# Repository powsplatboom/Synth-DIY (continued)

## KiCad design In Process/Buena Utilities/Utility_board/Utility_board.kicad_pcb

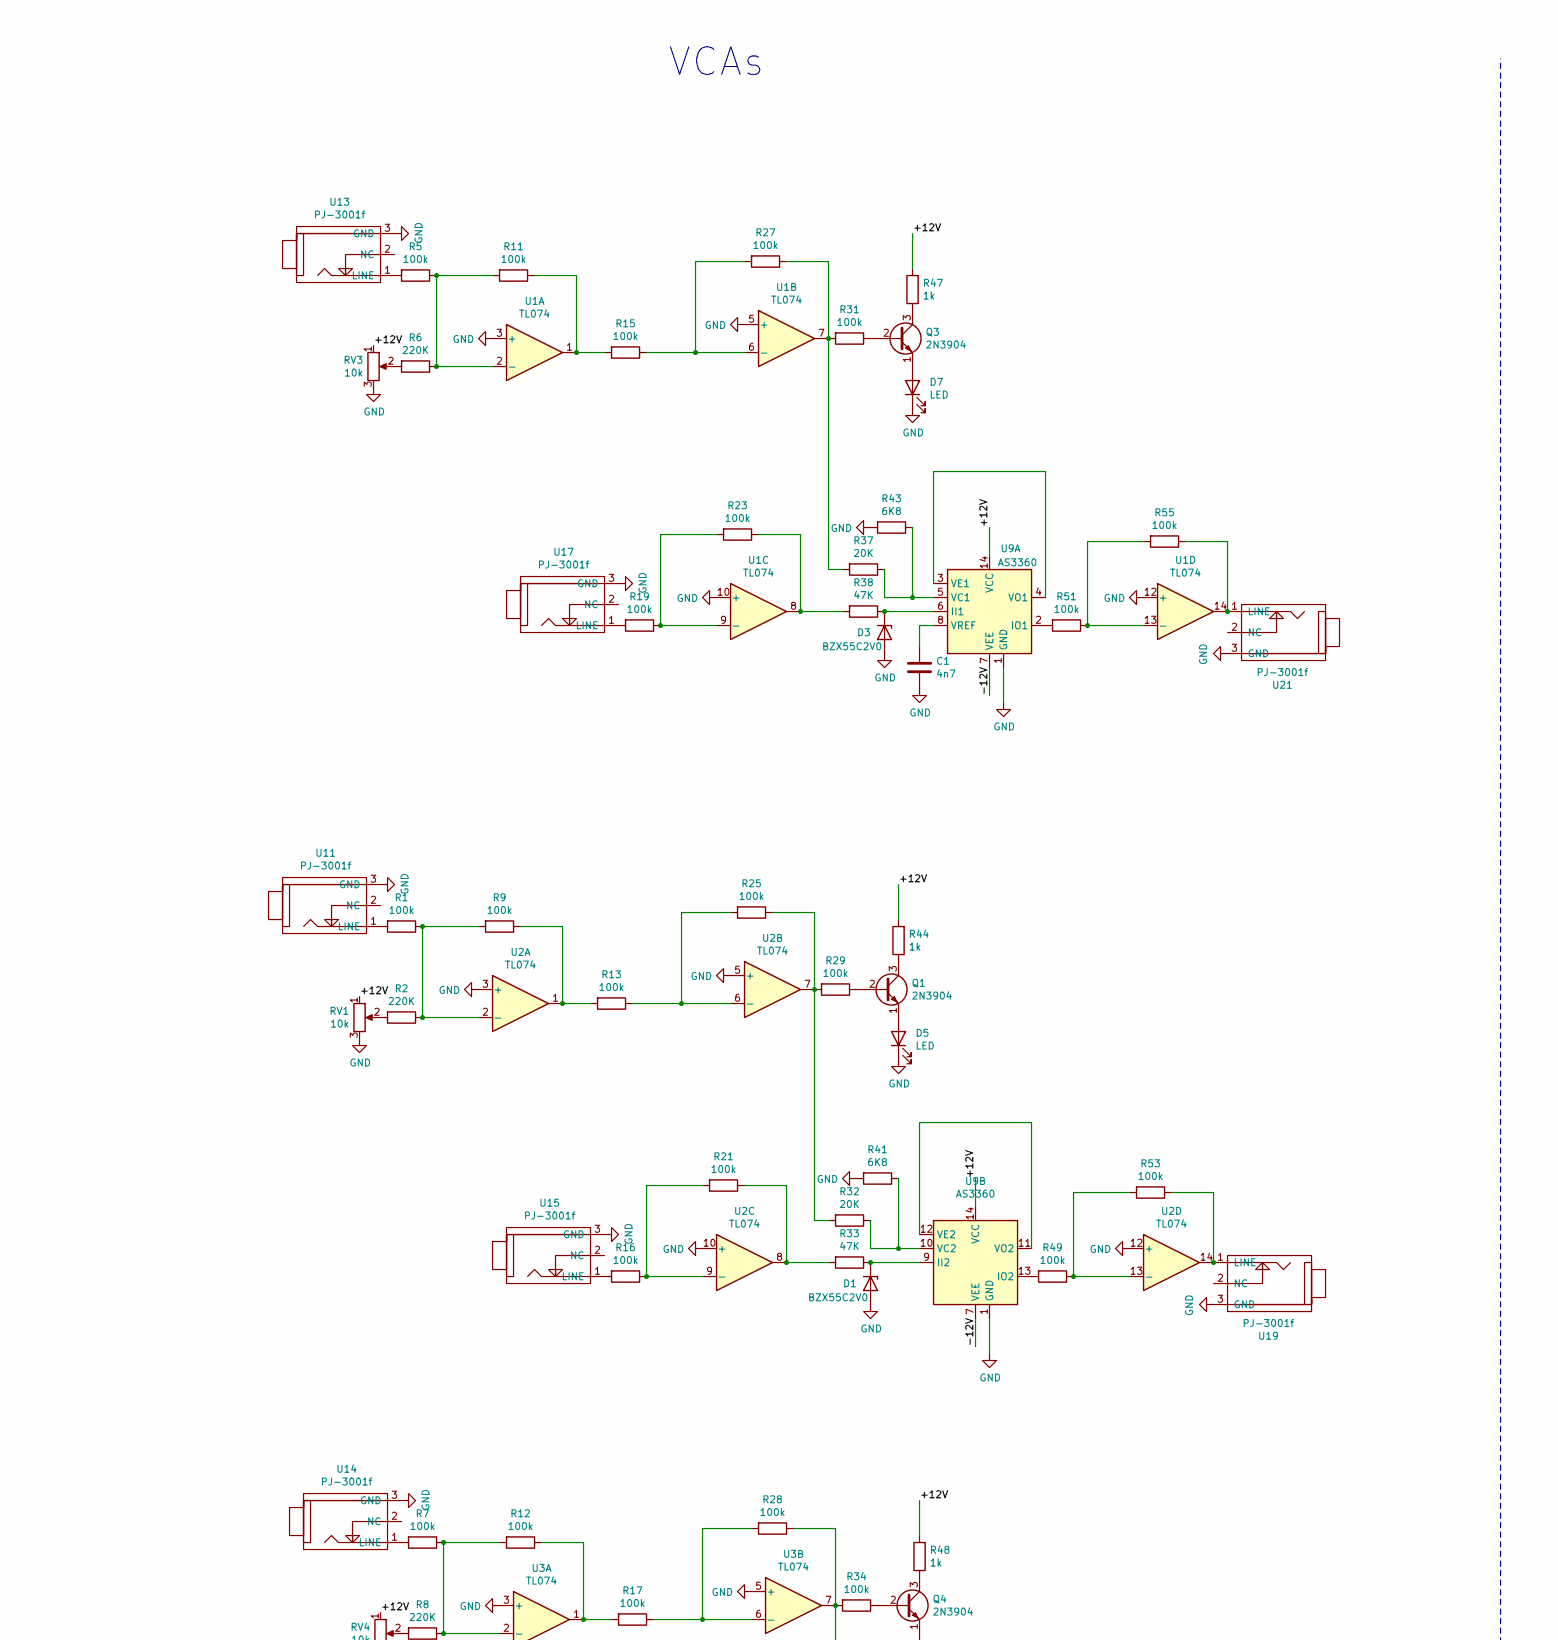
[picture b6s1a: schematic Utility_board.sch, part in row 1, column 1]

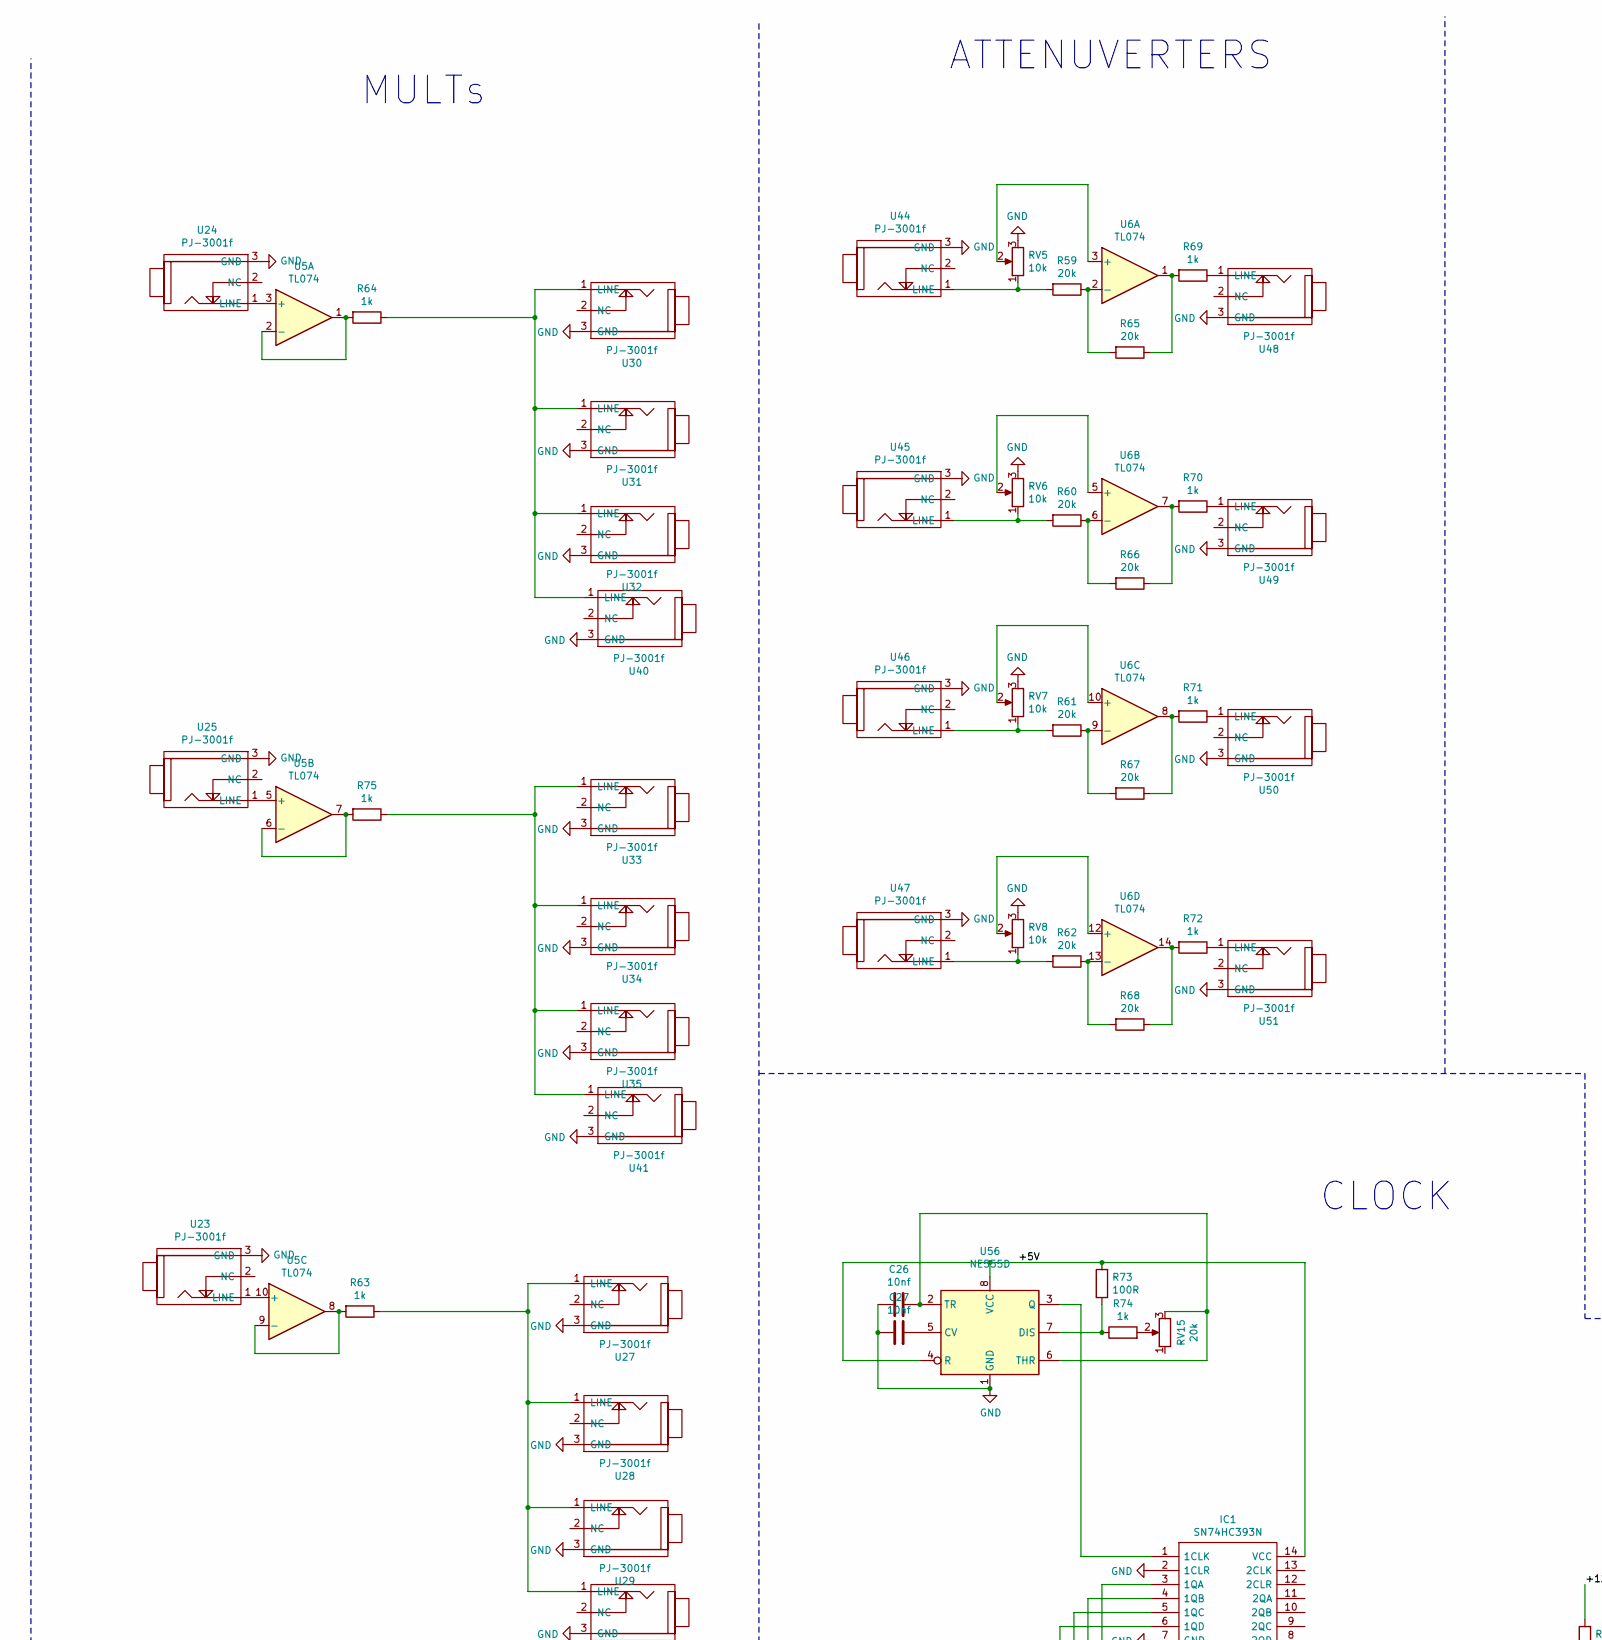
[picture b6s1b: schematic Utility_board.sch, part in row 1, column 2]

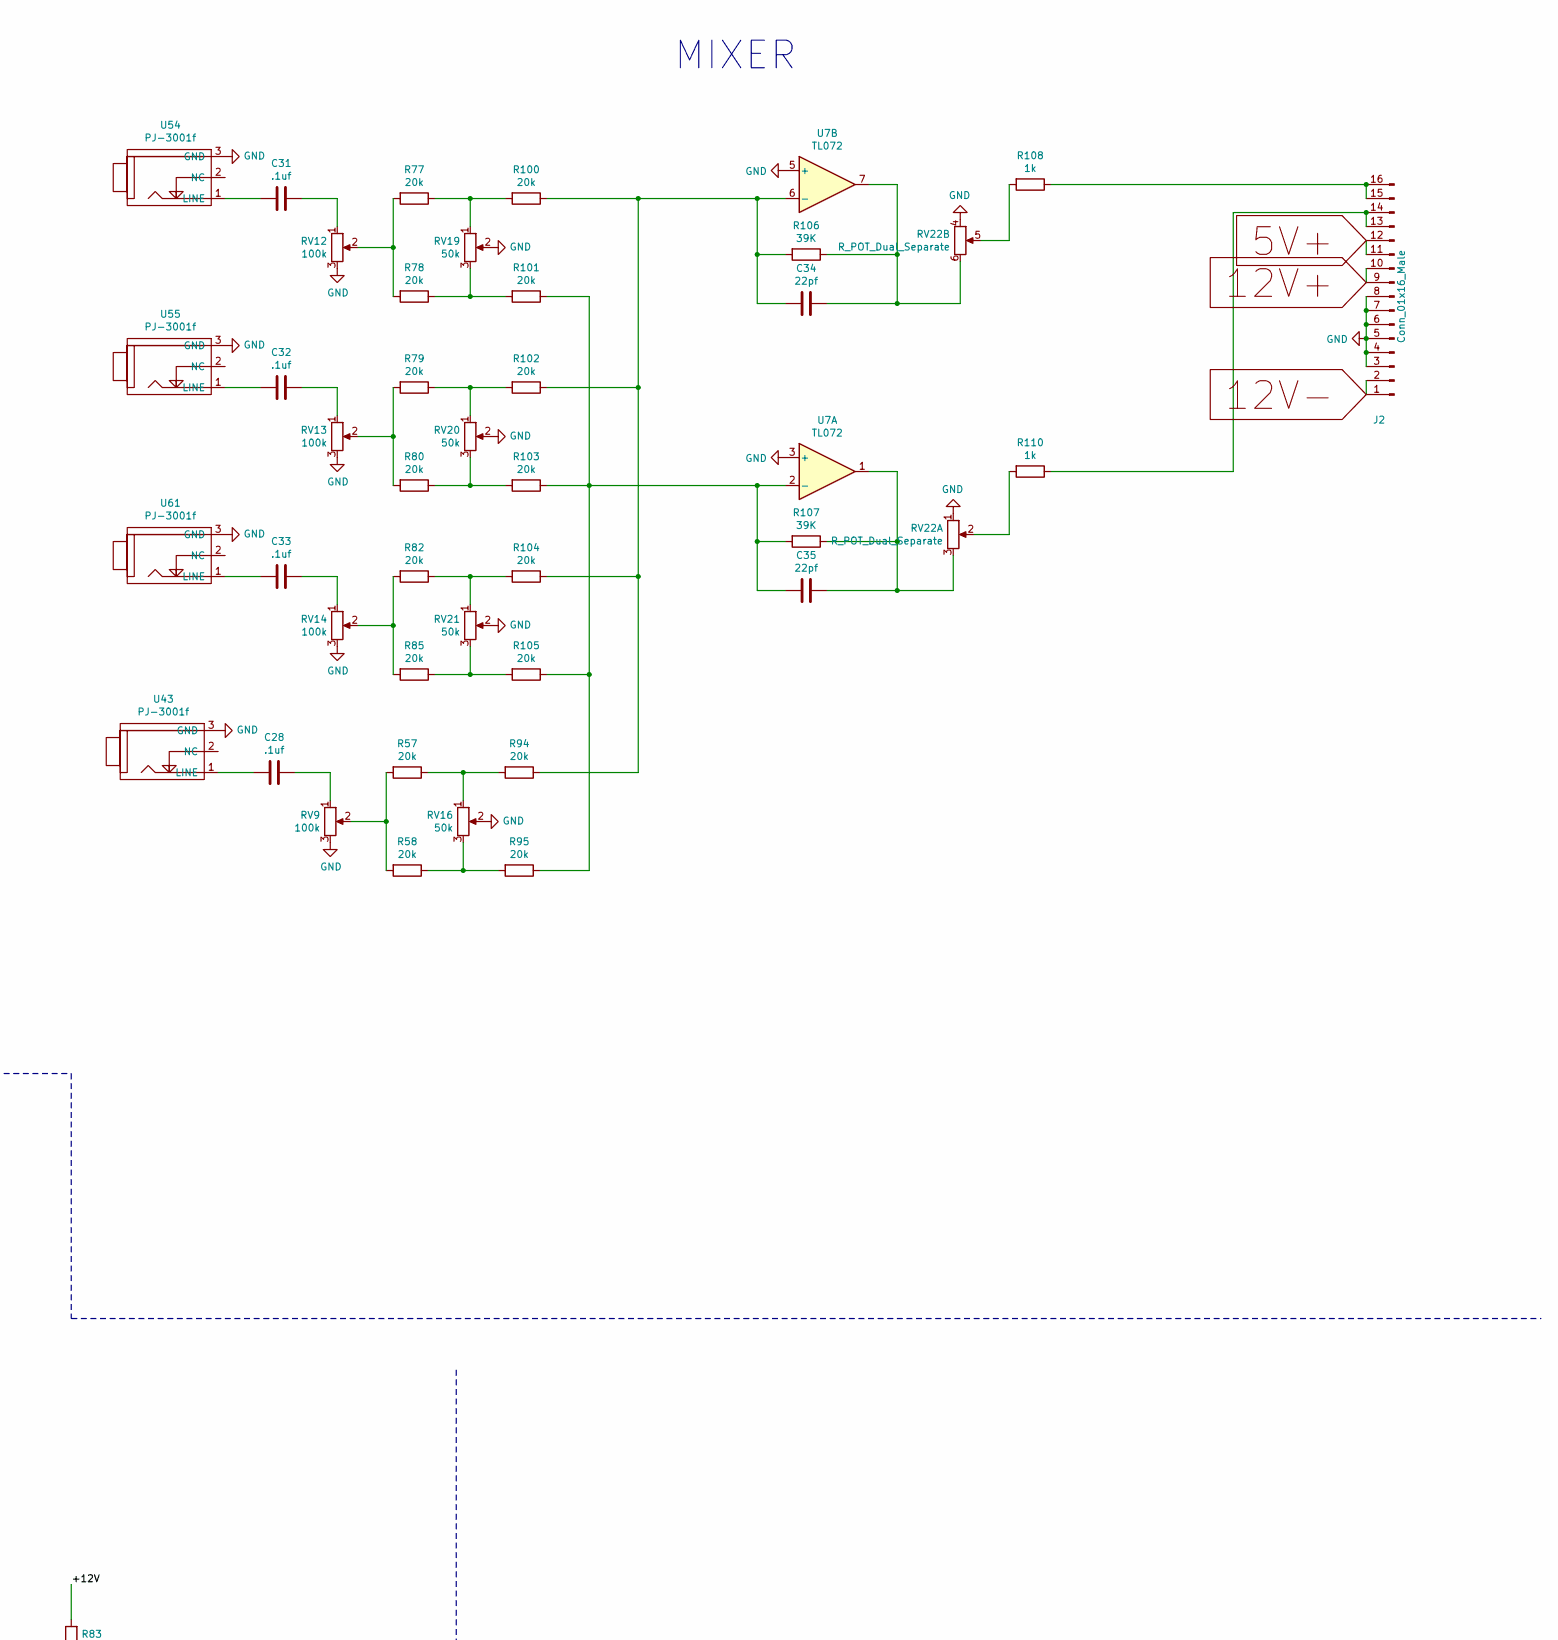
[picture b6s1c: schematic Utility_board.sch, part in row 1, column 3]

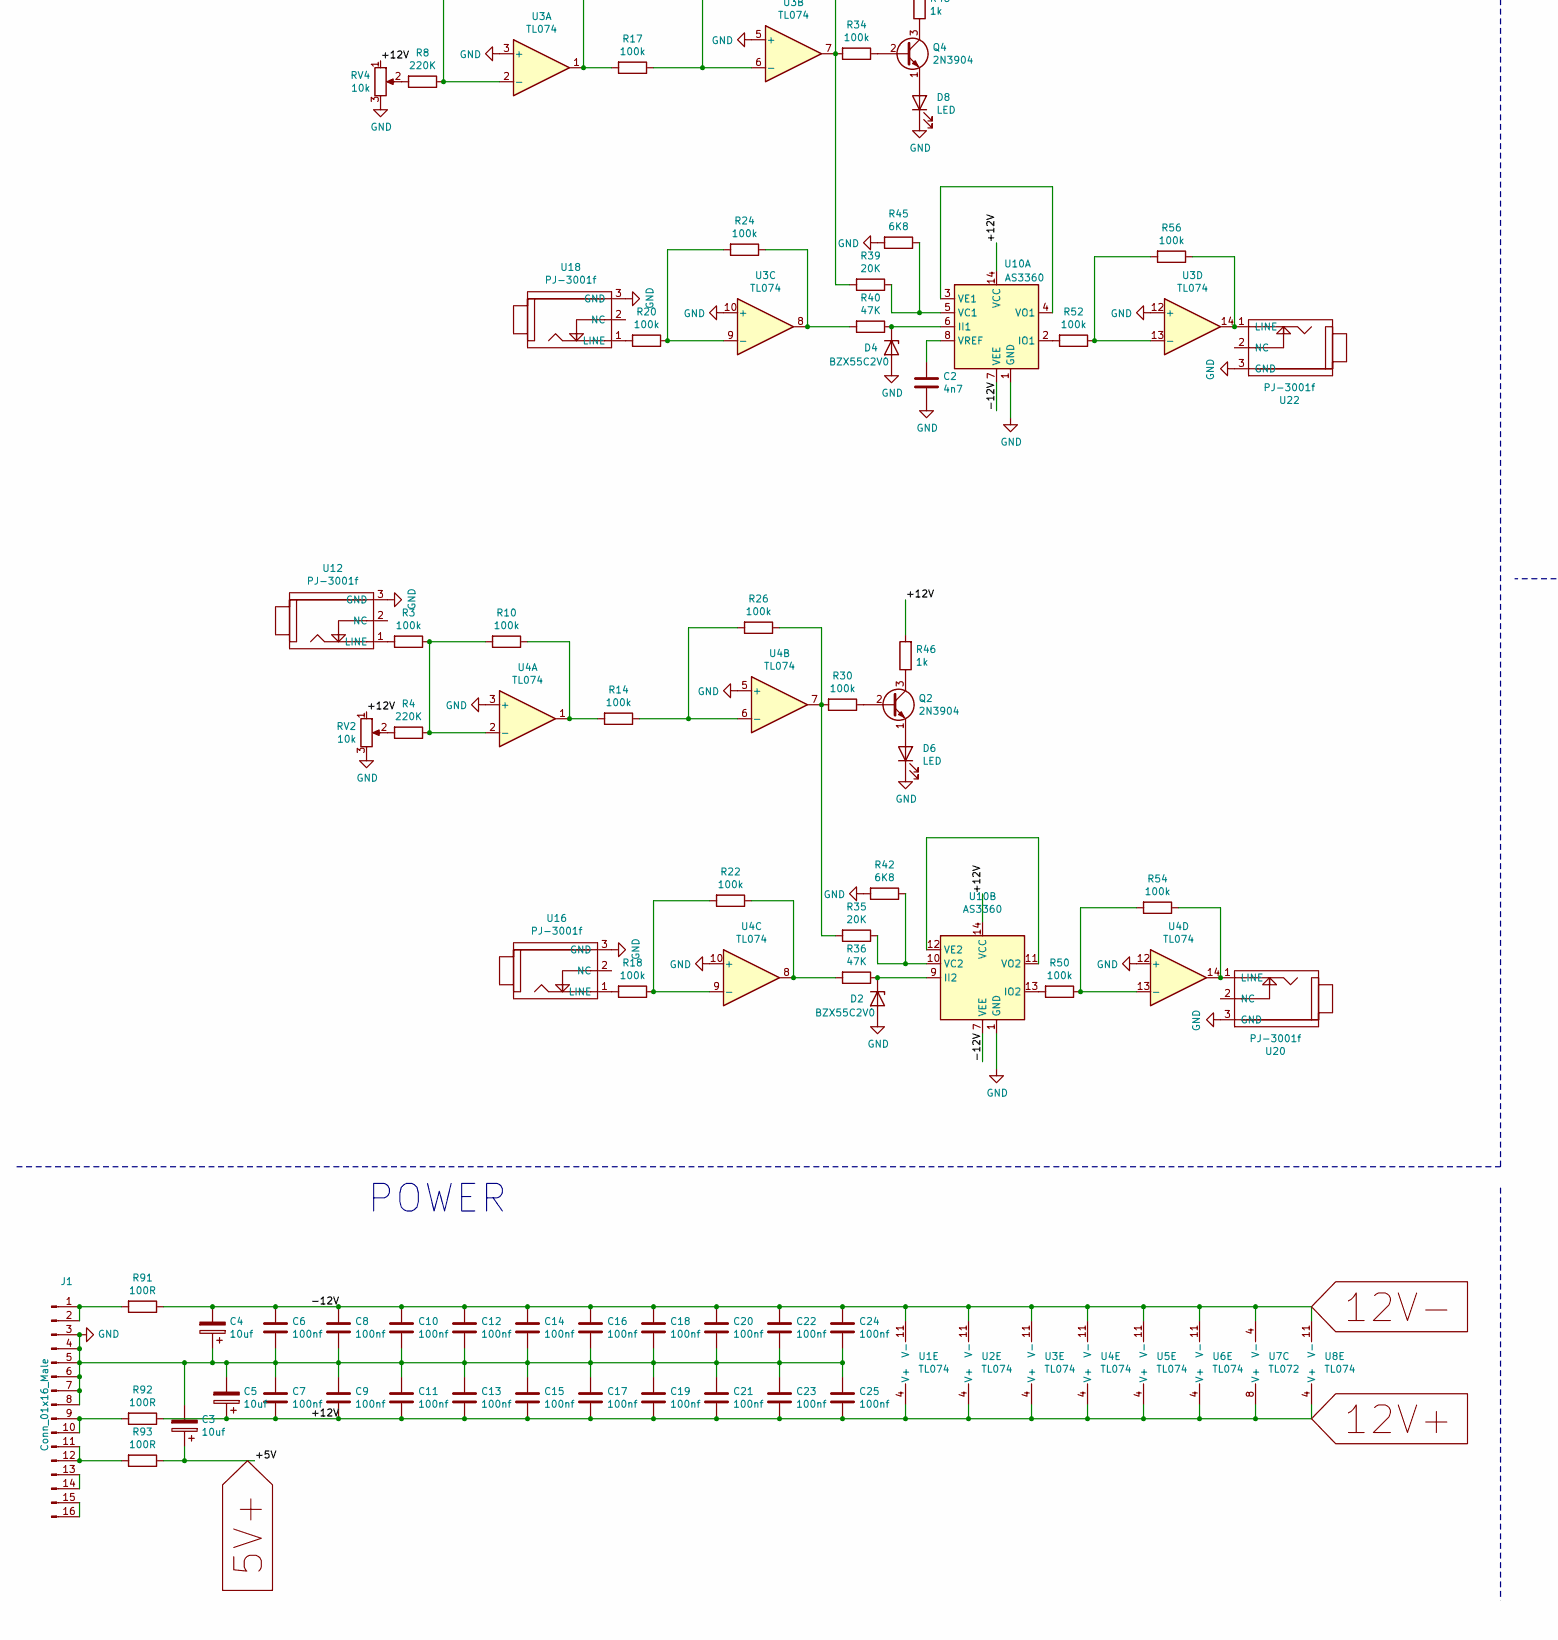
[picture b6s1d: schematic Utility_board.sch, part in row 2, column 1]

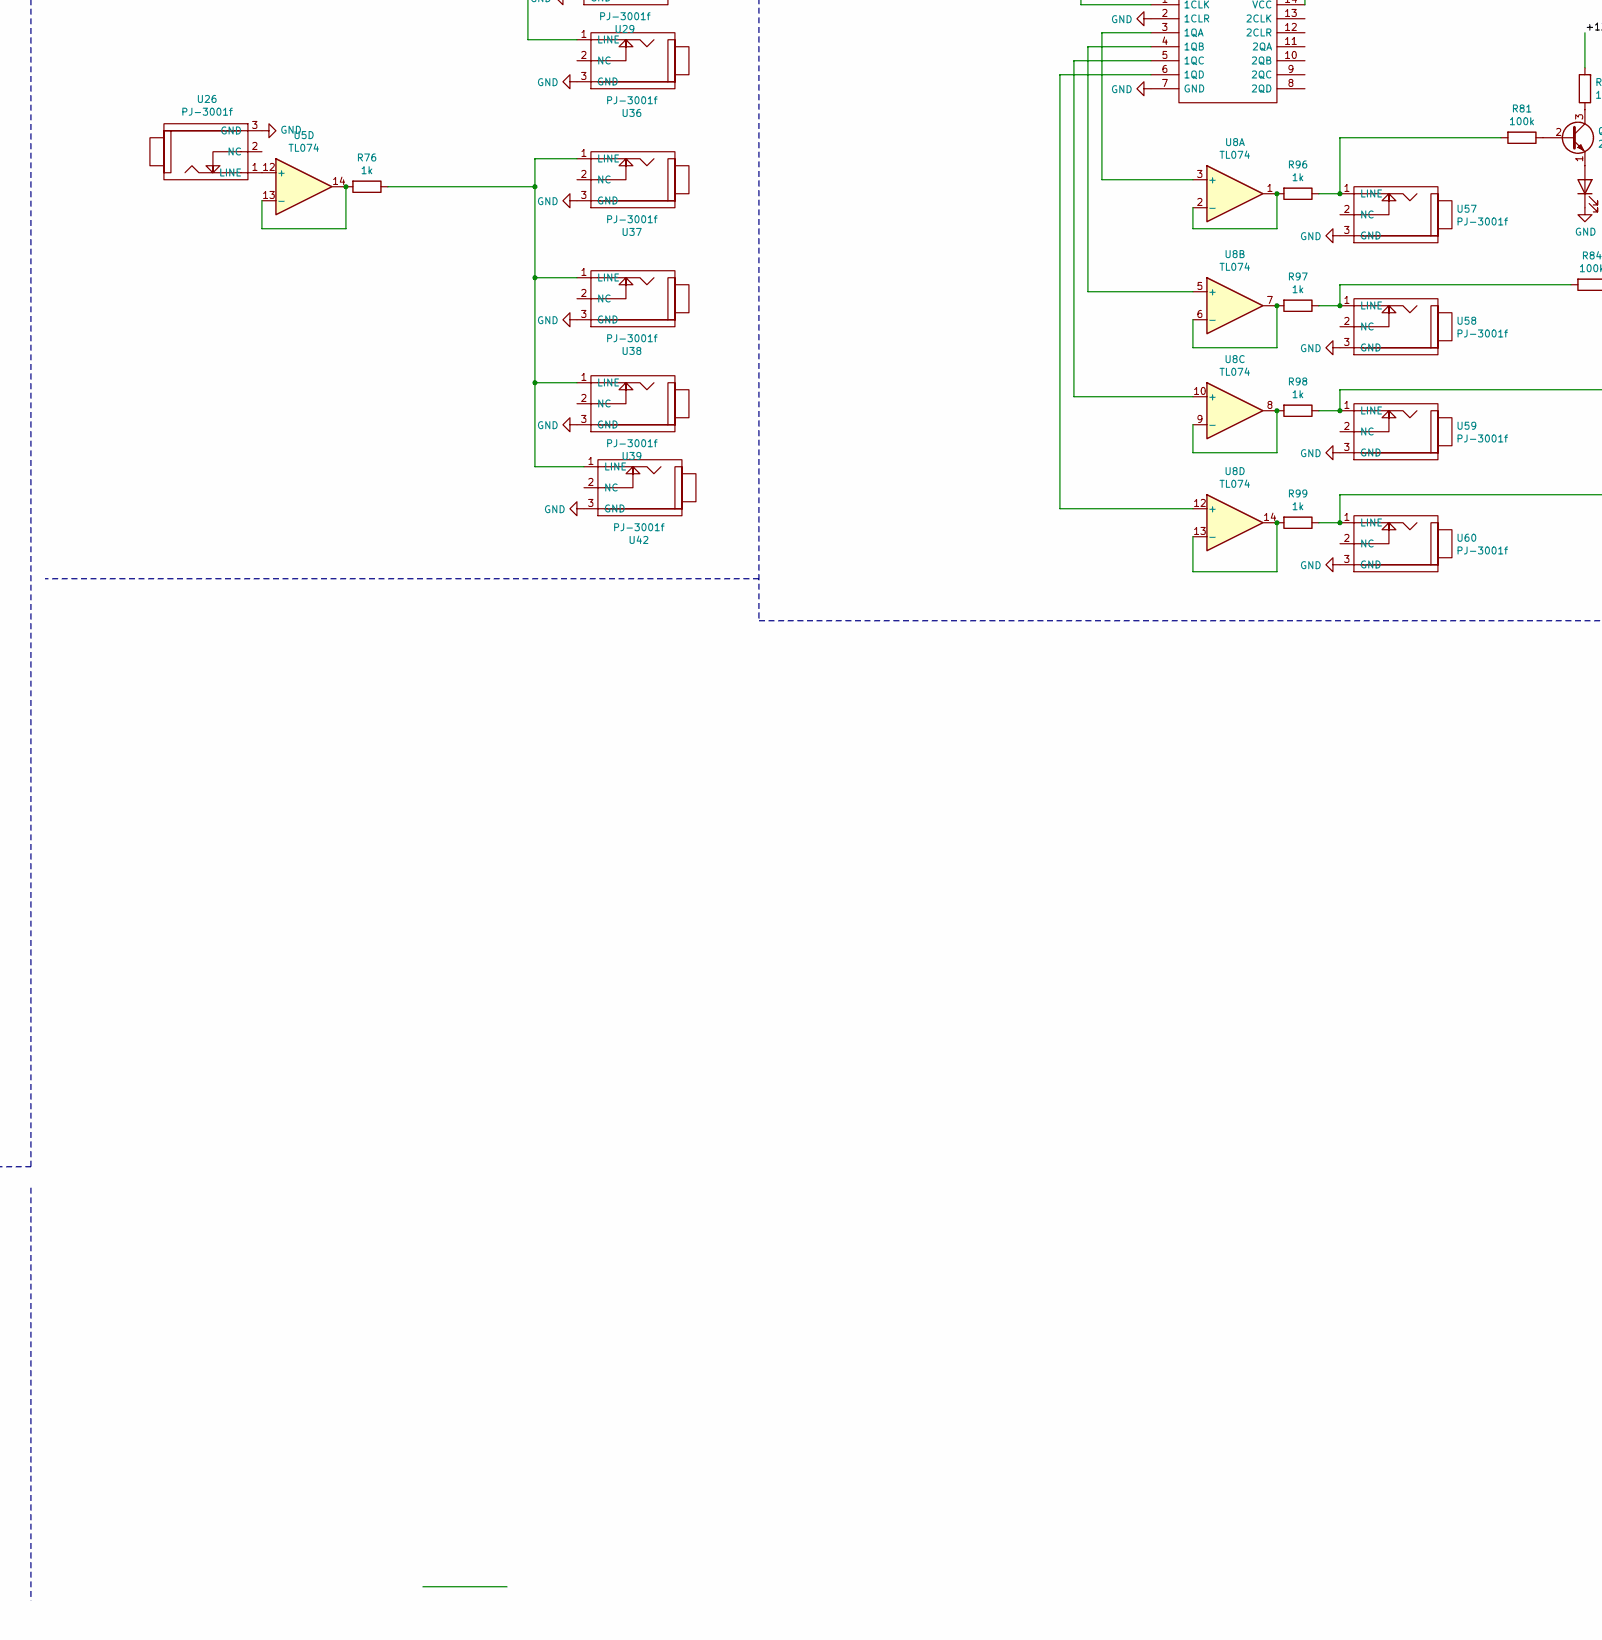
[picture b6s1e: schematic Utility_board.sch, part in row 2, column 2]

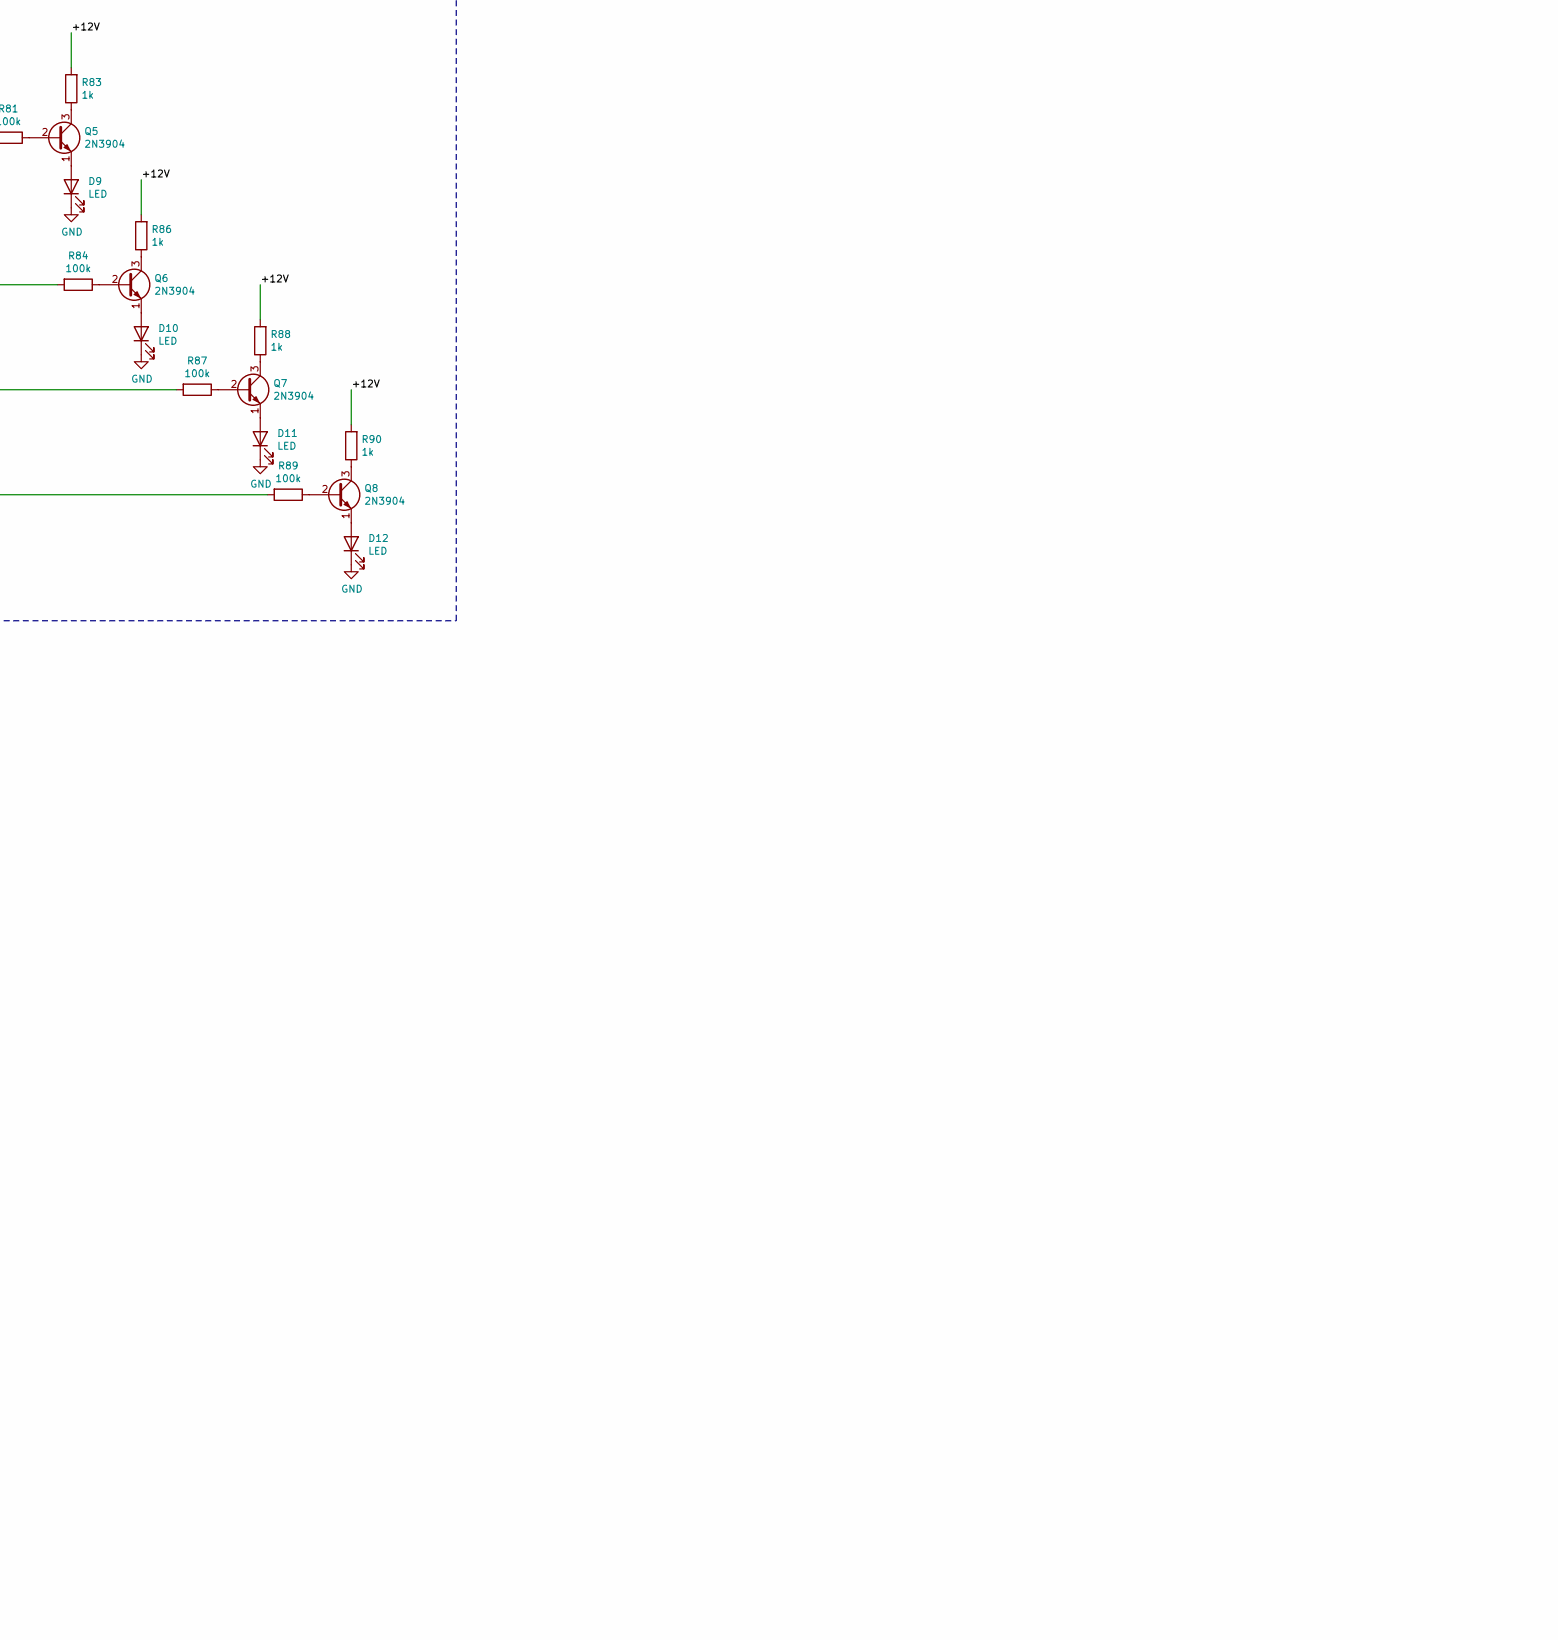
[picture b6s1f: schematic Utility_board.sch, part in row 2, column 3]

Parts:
C1, C2: 4n7; C_Disc_D4.3mm_W1.9mm_P5.00mm
C3, C4, C5: 10uf; CP_Radial_D5.0mm_P2.50mm
C6, C7, C8, C9, C10, C11, C12, C13, C14, C15, C16, C17, C18, C19, C20, C21, C22, C23, C24, C25: 100nf; C_Disc_D4.3mm_W1.9mm_P5.00mm
C26, C27: 10nf; C_Disc_D4.3mm_W1.9mm_P5.00mm
C28, C31, C32, C33: .1uf; C_Disc_D4.3mm_W1.9mm_P5.00mm
C34, C35: 22pf; C_Disc_D4.3mm_W1.9mm_P5.00mm
D1, D2, D3, D4: BZX55C2V0; D_DO-34_SOD68_P7.62mm_Horizontal
D5, D6, D7, D8, D9, D10, D11, D12: LED; LED_D5.0mm
IC1: SN74HC393N; DIP-14_W7.62mm_Socket; Manufacturer_Part_Number SN74HC393N; Mouser Part Number 595-SN74HC393N
J1, J2: Conn_01x16_Male; IDC-Header_2x08_P2.54mm_Vertical
Q1, Q2, Q3, Q4, Q5, Q6, Q7, Q8: 2N3904; TO-92_Inline
R1, R3, R5, R7, R9, R10, R11, R12, R13, R14, R15, R16, R17, R18, R19, R20, R21, R22, R23, R24, R25, R26, R27, R28, R29, R30, R31, R34, R49, R50, R51, R52, R53, R54, R55, R56, R81, R84, R87, R89: 100k; R_Axial_DIN0204_L3.6mm_D1.6mm_P7.62mm_Horizontal
R2, R4, R6, R8: 220K; R_Axial_DIN0204_L3.6mm_D1.6mm_P7.62mm_Horizontal
R32, R35, R37, R39: 20K; R_Axial_DIN0204_L3.6mm_D1.6mm_P7.62mm_Horizontal
R33, R36, R38, R40: 47K; R_Axial_DIN0204_L3.6mm_D1.6mm_P7.62mm_Horizontal
R41, R42, R43, R45: 6K8; R_Axial_DIN0204_L3.6mm_D1.6mm_P7.62mm_Horizontal
R44, R46, R47, R48, R63, R64, R69, R70, R71, R72, R74, R75, R76, R83, R86, R88, R90, R96, R97, R98, R99, R108, R110: 1k; R_Axial_DIN0204_L3.6mm_D1.6mm_P7.62mm_Horizontal
R57, R58, R59, R60, R61, R62, R65, R66, R67, R68, R77, R78, R79, R80, R82, R85, R94, R95, R100, R101, R102, R103, R104, R105: 20k; R_Axial_DIN0204_L3.6mm_D1.6mm_P7.62mm_Horizontal
R73, R91, R92, R93: 100R; R_Axial_DIN0204_L3.6mm_D1.6mm_P7.62mm_Horizontal
R106, R107: 39K; R_Axial_DIN0204_L3.6mm_D1.6mm_P7.62mm_Horizontal
RV1, RV2, RV3, RV4, RV5, RV6, RV7, RV8: 10k; Potentiometer_Alpha_RD901F-40-00D_Single_Vertical_CircularH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
RV9, RV12, RV13, RV14: 100k; Potentiometer_Alpha_RD901F-40-00D_Single_Vertical_CircularH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
RV15: 20k; Potentiometer_Alpha_RD901F-40-00D_Single_Vertical_CircularH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
RV16, RV19, RV20, RV21: 50k; Potentiometer_Alpha_RD901F-40-00D_Single_Vertical_CircularH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
RV22: R_POT_Dual_Separate; Potentiometer_Alpha_RD902F-40-00D_Dual_Vertical_CircularHol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
U1, U2, U3, U4, U5, U6, U8: TL074; DIP-14_W7.62mm_Socket
U7: TL072; DIP-8_W7.62mm_Socket
U9, U10: AS3360; DIP-14_W7.62mm_Socket
U11, U12, U13, U14, U15, U16, U17, U18, U19, U20, U21, U22, U23, U24, U25, U26, U27, U28, U29, U30, U31, U32, U33, U34, U35, U36, U37, U38, U39, U40, U41, U42, U43, U44, U45, U46, U47, U48, U49, U50, U51, U54, U55, U57, U58, U59, U60, U61: PJ-3001f; PJ-3001_Mono_Phone
U56: NE555D; DIP-8_W7.62mm_Socket

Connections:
5V+: C3.1, IC1.14 (VCC), J2.11, J2.12, R73.2, R93.1, U56.4 (R), U56.8 (VCC)
12V+: C5.1, C7.2, C9.2, C11.2, C13.2, C15.2, C17.2, C19.2, C21.2, C23.2, C25.2, J2.9, J2.10, R44.2, R46.2, R47.2, R48.2, R83.2, R86.2, R88.2, R90.2, R92.1, RV1.1, RV2.1, RV3.1, RV4.1, U1.4 (V+), U2.4 (V+), U3.4 (V+), U4.4 (V+), U5.4 (V+), U6.4 (V+), U7.8 (V+), U8.4 (V+), U9.14 (VCC), U10.14 (VCC)
12V-: C4.2, C6.1, C8.1, C10.1, C12.1, C14.1, C16.1, C18.1, C20.1, C22.1, C24.1, J2.1, J2.2, R91.1, U1.11 (V-), U2.11 (V-), U3.11 (V-), U4.11 (V-), U5.11 (V-), U6.11 (V-), U7.4 (V-), U8.11 (V-), U9.7 (VEE), U10.7 (VEE)
GND: C1.2, C2.2, C3.2, C4.1, C5.2, C6.2, C7.1, C8.2, C9.1, C10.2, C11.1, C12.2, C13.1, C14.2, C15.1, C16.2, C17.1, C18.2, C19.1, C20.2, C21.1, C22.2, C23.1, C24.2, C25.1, C26.2, C27.2, D1.2 (A), D2.2 (A), D3.2 (A), D4.2 (A), D5.1 (K), D6.1 (K), D7.1 (K), D8.1 (K), D9.1 (K), D10.1 (K), D11.1 (K), D12.1 (K), IC1.2 (1CLR), IC1.7 (GND), J1.3, J1.4, J1.5, J1.6, J1.7, J1.8, J2.3, J2.4, J2.5, J2.6, J2.7, J2.8, R41.2, R42.2, R43.2, R45.2, RV1.3, RV2.3, RV3.3, RV4.3, RV5.3, RV6.3, RV7.3, RV8.3, RV9.3, RV12.3, RV13.3, RV14.3, RV16.2, RV19.2, RV20.2, RV21.2, RV22.1, RV22.4, U1.3 (+), U1.5 (+), U1.10 (+), U1.12 (+), U2.3 (+), U2.5 (+), U2.10 (+), U2.12 (+), U3.3 (+), U3.5 (+), U3.10 (+), U3.12 (+), U4.3 (+), U4.5 (+), U4.10 (+), U4.12 (+), U7.3 (+), U7.5 (+), U9.1 (GND), U10.1 (GND), U11.3 (GND), U12.3 (GND), U13.3 (GND), U14.3 (GND), U15.3 (GND), U16.3 (GND), U17.3 (GND), U18.3 (GND), U19.3 (GND), U20.3 (GND), U21.3 (GND), U22.3 (GND), U23.3 (GND), U24.3 (GND), U25.3 (GND), U26.3 (GND), U27.3 (GND), U28.3 (GND), U29.3 (GND), U30.3 (GND), U31.3 (GND), U32.3 (GND), U33.3 (GND), U34.3 (GND), U35.3 (GND), U36.3 (GND), U37.3 (GND), U38.3 (GND), U39.3 (GND), U40.3 (GND), U41.3 (GND), U42.3 (GND), U43.3 (GND), U44.3 (GND), U45.3 (GND), U46.3 (GND), U47.3 (GND), U48.3 (GND), U49.3 (GND), U50.3 (GND), U51.3 (GND), U54.3 (GND), U55.3 (GND), U56.1 (GND), U57.3 (GND), U58.3 (GND), U59.3 (GND), U60.3 (GND), U61.3 (GND)
unnamed: C1.1, U9.8 (VREF)
unnamed: C2.1, U10.8 (VREF)
unnamed: C26.1, RV15.3, U56.2 (TR), U56.6 (THR)
unnamed: C27.1, U56.5 (CV)
unnamed: C28.1, RV9.1
unnamed: C28.2, U43.1 (LINE)
unnamed: C31.1, RV12.1
unnamed: C31.2, U54.1 (LINE)
unnamed: C32.1, RV13.1
unnamed: C32.2, U55.1 (LINE)
unnamed: C33.1, RV14.1
unnamed: C33.2, U61.1 (LINE)
unnamed: C34.1, R106.1, RV22.6, U7.7
unnamed: C34.2, R94.1, R100.1, R102.1, R104.1, R106.2, U7.6 (-)
unnamed: C35.1, R107.1, RV22.3, U7.1
unnamed: C35.2, R95.1, R101.1, R103.1, R105.1, R107.2, U7.2 (-)
unnamed: D1.1 (K), R33.1, U9.9 (II2)
unnamed: D2.1 (K), R36.1, U10.9 (II2)
unnamed: D3.1 (K), R38.1, U9.6 (II1)
unnamed: D4.1 (K), R40.1, U10.6 (II1)
unnamed: D5.2 (A), Q1.1 (E)
unnamed: D6.2 (A), Q2.1 (E)
unnamed: D7.2 (A), Q3.1 (E)
unnamed: D8.2 (A), Q4.1 (E)
unnamed: D9.2 (A), Q5.1 (E)
unnamed: D10.2 (A), Q6.1 (E)
unnamed: D11.2 (A), Q7.1 (E)
unnamed: D12.2 (A), Q8.1 (E)
unnamed: IC1.1 (1CLK), U56.3 (Q)
unnamed: IC1.3 (1QA), U8.3 (+)
unnamed: IC1.4 (1QB), U8.5 (+)
unnamed: IC1.5 (1QC), U8.10 (+)
unnamed: IC1.6 (1QD), U8.12 (+)
unnamed: J1.1, J1.2, R91.2
unnamed: J1.9, J1.10, R92.2
unnamed: J1.11, J1.12, R93.2
unnamed: J1.13, J1.14
unnamed: J1.15, J1.16
unnamed: J2.13, J2.14, R110.1
unnamed: J2.15, J2.16, R108.1
unnamed: Q1.2 (B), R29.1
unnamed: Q1.3 (C), R44.1
unnamed: Q2.2 (B), R30.1
unnamed: Q2.3 (C), R46.1
unnamed: Q3.2 (B), R31.1
unnamed: Q3.3 (C), R47.1
unnamed: Q4.2 (B), R34.1
unnamed: Q4.3 (C), R48.1
unnamed: Q5.2 (B), R81.1
unnamed: Q5.3 (C), R83.1
unnamed: Q6.2 (B), R84.1
unnamed: Q6.3 (C), R86.1
unnamed: Q7.2 (B), R87.1
unnamed: Q7.3 (C), R88.1
unnamed: Q8.2 (B), R89.1
unnamed: Q8.3 (C), R90.1
unnamed: R1.1, R2.1, R9.2, U2.2 (-)
unnamed: R1.2, U11.1 (LINE)
unnamed: R2.2, RV1.2
unnamed: R3.2, U12.1 (LINE)
unnamed: R4.2, RV2.2
unnamed: R5.2, U13.1 (LINE)
unnamed: R6.2, RV3.2
unnamed: R7.2, U14.1 (LINE)
unnamed: R8.2, RV4.2
unnamed: R10.1, R14.2, U4.1
unnamed: R3.1, R4.1, R10.2, U4.2 (-)
unnamed: R11.1, R15.2, U1.1
unnamed: R5.1, R6.1, R11.2, U1.2 (-)
unnamed: R12.1, R17.2, U3.1
unnamed: R7.1, R8.1, R12.2, U3.2 (-)
unnamed: R13.1, R25.2, U2.6 (-)
unnamed: R9.1, R13.2, U2.1
unnamed: R14.1, R26.2, U4.6 (-)
unnamed: R15.1, R27.2, U1.6 (-)
unnamed: R16.1, R21.2, U2.9 (-)
unnamed: R16.2, U15.1 (LINE)
unnamed: R17.1, R28.2, U3.6 (-)
unnamed: R18.1, R22.2, U4.9 (-)
unnamed: R18.2, U16.1 (LINE)
unnamed: R19.1, R23.2, U1.9 (-)
unnamed: R19.2, U17.1 (LINE)
unnamed: R20.1, R24.2, U3.9 (-)
unnamed: R20.2, U18.1 (LINE)
unnamed: R21.1, R33.2, U2.8
unnamed: R22.1, R36.2, U4.8
unnamed: R23.1, R38.2, U1.8
unnamed: R24.1, R40.2, U3.8
unnamed: R25.1, R29.2, R32.2, U2.7
unnamed: R26.1, R30.2, R35.2, U4.7
unnamed: R27.1, R31.2, R37.2, U1.7
unnamed: R28.1, R34.2, R39.2, U3.7
unnamed: R32.1, R41.1, U9.10 (VC2)
unnamed: R35.1, R42.1, U10.10 (VC2)
unnamed: R37.1, R43.1, U9.5 (VC1)
unnamed: R39.1, R45.1, U10.5 (VC1)
unnamed: R49.1, R53.2, U2.13 (-)
unnamed: R49.2, U9.13 (IO2)
unnamed: R50.1, R54.2, U4.13 (-)
unnamed: R50.2, U10.13 (IO2)
unnamed: R51.1, R55.2, U1.13 (-)
unnamed: R51.2, U9.2 (IO1)
unnamed: R52.1, R56.2, U3.13 (-)
unnamed: R52.2, U10.2 (IO1)
unnamed: R53.1, U2.14, U19.1 (LINE)
unnamed: R54.1, U4.14, U20.1 (LINE)
unnamed: R55.1, U1.14, U21.1 (LINE)
unnamed: R56.1, U3.14, U22.1 (LINE)
unnamed: R57.1, R94.2, RV16.1
unnamed: R57.2, R58.2, RV9.2
unnamed: R58.1, R95.2, RV16.3
unnamed: R59.1, R65.2, U6.2 (-)
unnamed: R59.2, RV5.1, U44.1 (LINE)
unnamed: R60.1, R66.2, U6.6 (-)
unnamed: R60.2, RV6.1, U45.1 (LINE)
unnamed: R61.1, R67.2, U6.9 (-)
unnamed: R61.2, RV7.1, U46.1 (LINE)
unnamed: R62.1, R68.2, U6.13 (-)
unnamed: R62.2, RV8.1, U47.1 (LINE)
unnamed: R63.1, U27.1 (LINE), U28.1 (LINE), U29.1 (LINE), U36.1 (LINE)
unnamed: R63.2, U5.8, U5.9 (-)
unnamed: R64.1, U30.1 (LINE), U31.1 (LINE), U32.1 (LINE), U40.1 (LINE)
unnamed: R64.2, U5.1, U5.2 (-)
unnamed: R65.1, R69.2, U6.1
unnamed: R66.1, R70.2, U6.7
unnamed: R67.1, R71.2, U6.8
unnamed: R68.1, R72.2, U6.14
unnamed: R69.1, U48.1 (LINE)
unnamed: R70.1, U49.1 (LINE)
unnamed: R71.1, U50.1 (LINE)
unnamed: R72.1, U51.1 (LINE)
unnamed: R73.1, R74.1, U56.7 (DIS)
unnamed: R74.2, RV15.2
unnamed: R75.1, U33.1 (LINE), U34.1 (LINE), U35.1 (LINE), U41.1 (LINE)
unnamed: R75.2, U5.6 (-), U5.7
unnamed: R76.1, U37.1 (LINE), U38.1 (LINE), U39.1 (LINE), U42.1 (LINE)
unnamed: R76.2, U5.13 (-), U5.14
unnamed: R77.2, R78.2, RV12.2
unnamed: R79.2, R80.2, RV13.2
unnamed: R81.2, R96.1, U57.1 (LINE)
unnamed: R82.2, R85.2, RV14.2
unnamed: R84.2, R97.1, U58.1 (LINE)
unnamed: R87.2, R98.1, U59.1 (LINE)
unnamed: R89.2, R99.1, U60.1 (LINE)
unnamed: R96.2, U8.1, U8.2 (-)
unnamed: R97.2, U8.6 (-), U8.7
unnamed: R98.2, U8.8, U8.9 (-)
unnamed: R99.2, U8.13 (-), U8.14
unnamed: R77.1, R100.2, RV19.1
unnamed: R78.1, R101.2, RV19.3
unnamed: R79.1, R102.2, RV20.1
unnamed: R80.1, R103.2, RV20.3
unnamed: R82.1, R104.2, RV21.1
unnamed: R85.1, R105.2, RV21.3
unnamed: R108.2, RV22.5
unnamed: R110.2, RV22.2
unnamed: RV5.2, U6.3 (+)
unnamed: RV6.2, U6.5 (+)
unnamed: RV7.2, U6.10 (+)
unnamed: RV8.2, U6.12 (+)
unnamed: U9.3 (VE1), U9.4 (VO1)
unnamed: U9.11 (VO2), U9.12 (VE2)
unnamed: U10.3 (VE1), U10.4 (VO1)
unnamed: U10.11 (VO2), U10.12 (VE2)
unnamed: U5.10 (+), U23.1 (LINE)
unnamed: U5.3 (+), U24.1 (LINE)
unnamed: U5.5 (+), U25.1 (LINE)
unnamed: U5.12 (+), U26.1 (LINE)

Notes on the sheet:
VCAs
MULTs
ATTENUVERTERS
CLOCK
POWER
MIXER

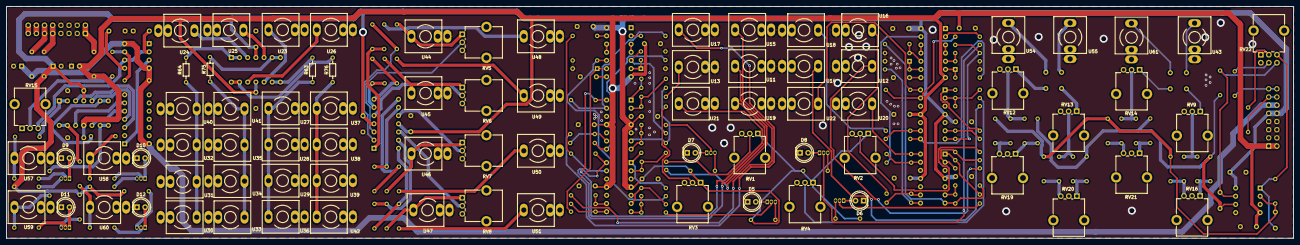
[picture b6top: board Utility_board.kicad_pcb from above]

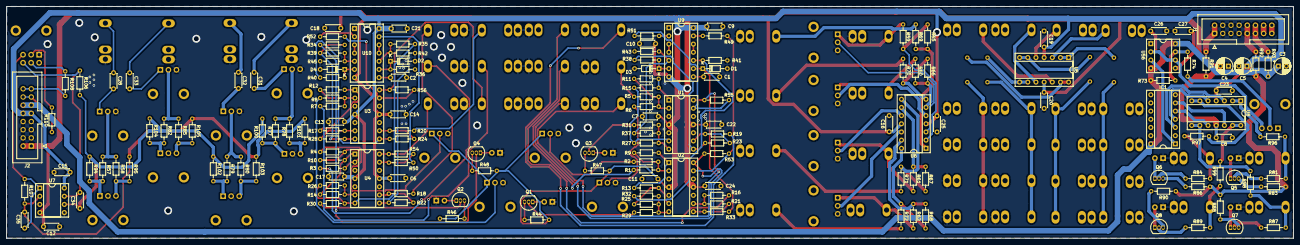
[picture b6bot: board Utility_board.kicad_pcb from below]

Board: 2 copper layers, 399.8 x 72.0 mm, 242 parts (164 on the bottom side), 172 nets.
